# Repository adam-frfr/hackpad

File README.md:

# Hackpad

## Overview
3-key macropad using Seeed XIAO RP2040.

## Schematic

## PCB

## CAD

## Bill of Materials

 Part                  Quantity

 Seeed XIAO RP2040        1 
 MX Switches              3 
 Keycaps                  3
 M3x16 Screws             4 
 M3 Heatset Inserts       4

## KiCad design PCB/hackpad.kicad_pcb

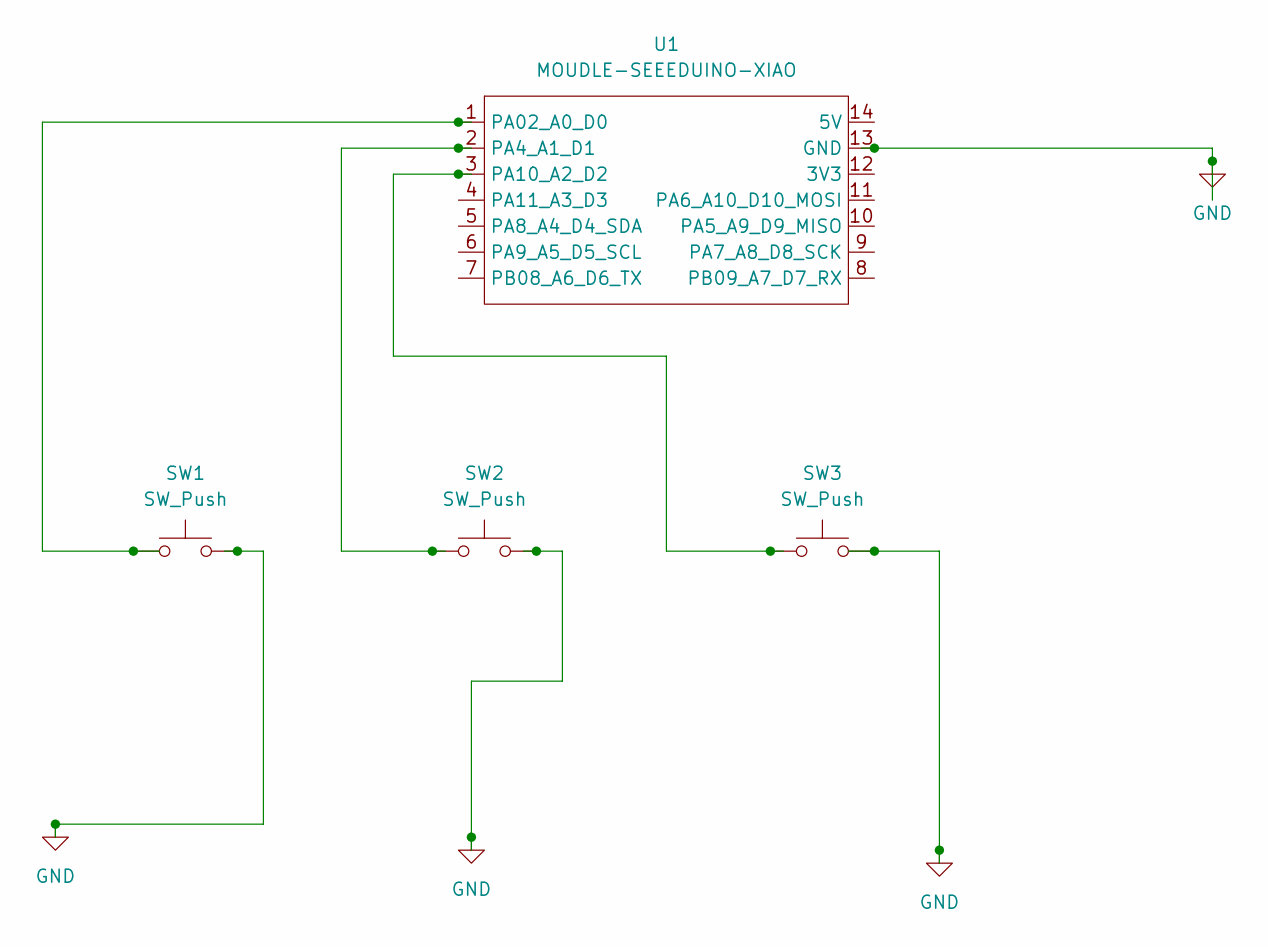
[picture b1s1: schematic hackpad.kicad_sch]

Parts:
SW1, SW2, SW3: SW_Push; SW_Cherry_MX_1.00u_PCB
U1: MOUDLE-SEEEDUINO-XIAO; XIAO-Generic-Hybrid-14P-2.54-21X17.8MM

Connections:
GND: SW1.2, SW2.2, SW3.2, U1.13 (GND)
unnamed: SW1.1, U1.1 (PA02_A0_D0)
unnamed: SW2.1, U1.2 (PA4_A1_D1)
unnamed: SW3.1, U1.3 (PA10_A2_D2)

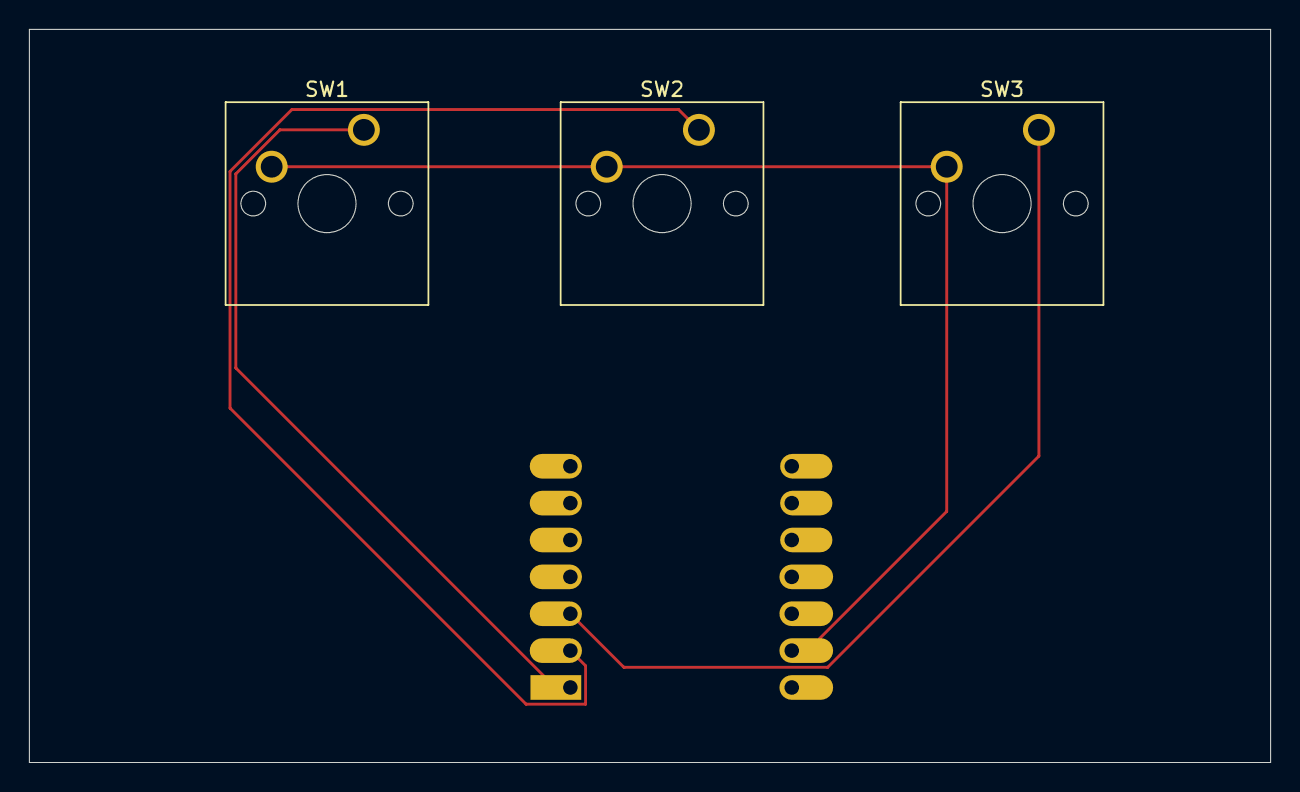
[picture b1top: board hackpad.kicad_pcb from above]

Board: 2 copper layers, 85.5 x 50.5 mm, 4 parts (1 on the bottom side), 4 nets.
